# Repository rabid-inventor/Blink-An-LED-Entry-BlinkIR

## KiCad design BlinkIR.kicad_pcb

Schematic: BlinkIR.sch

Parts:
D1, D2, D3, D4: LED; LED_0805
J1, J2, J3: Conn_01x01; MountingHole_4.3mm_M4_ISO7380_Pad
Q1, Q2, Q3: Q_Photo_NPN; LED_D3.0mm_Horizontal_O1.27mm_Z2.0mm
R1, R3: 330R; R_0603
R2, R4: 10K; R_0603
TP1, TP2, TP3, TP4, TP5: TestPoint; Measurement_Point_Round-SMD-Pad_Small
U1: ATtiny10-TS; SOT-23-6

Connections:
/BLINK: R1.1, U1.4 (PB2)
/RESET: R2.1, TP2.1, U1.6 (~RESET~/PB3)
/SENCE_BLINK: Q1.1, Q2.1, Q3.1, R4.2, TP3.1, U1.1 (PB0)
/SEND_BLINK: D2.1, D3.1, D4.1, TP4.1, U1.3 (PB1)
GND: D1.1, J3.1, Q1.2, Q2.2, Q3.2, TP5.1, U1.2 (GND)
unnamed: D1.2, R1.2
unnamed: D2.2, D3.2, D4.2, R3.2
VCC: J1.1, J2.1, R2.2, R3.1, R4.1, TP1.1, U1.5 (VCC)

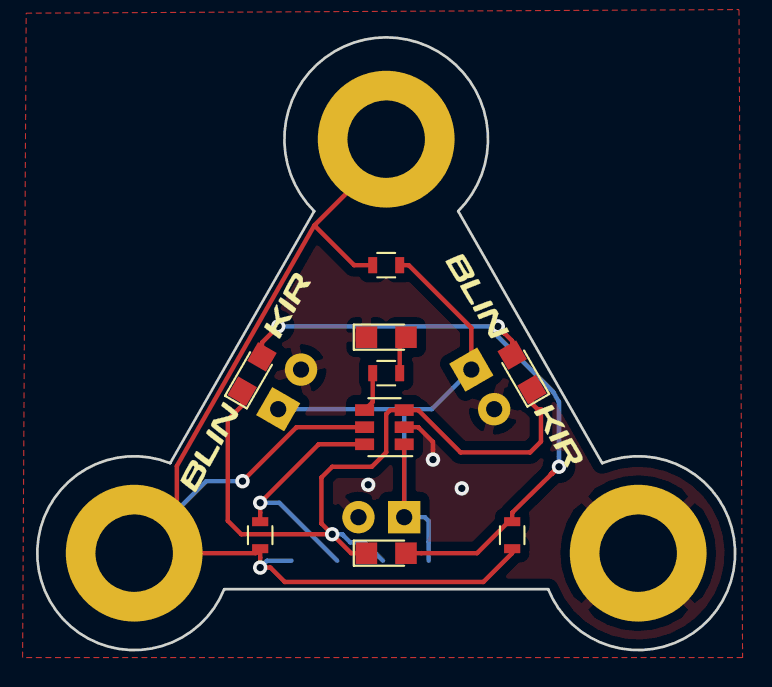
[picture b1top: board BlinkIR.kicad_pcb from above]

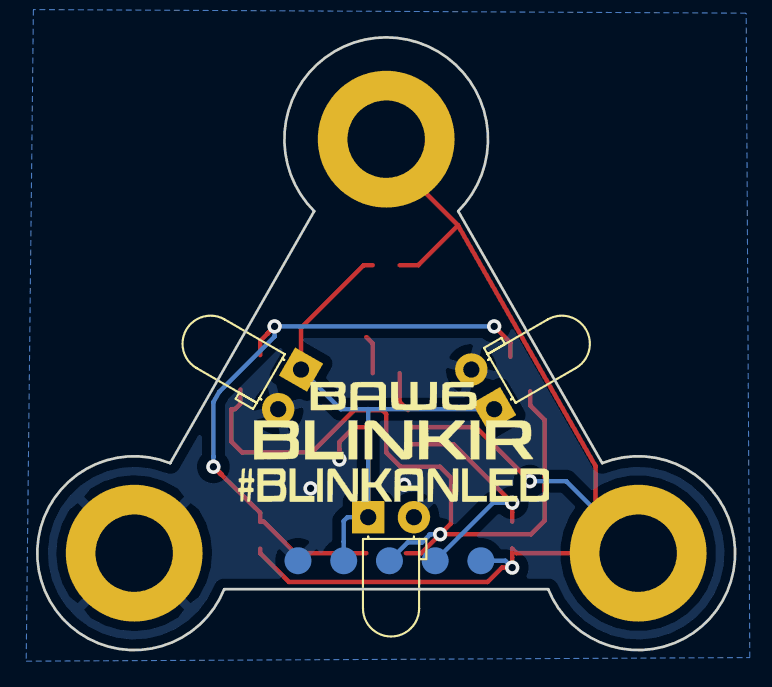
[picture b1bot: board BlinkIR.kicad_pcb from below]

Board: 2 copper layers, 38.8 x 34.0 mm, 20 parts (8 on the bottom side), 8 nets.

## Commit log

2018-08-29 Added initail files from board a week repo
2018-08-29 Project rename to BlinkIR
2018-08-31 started firmware
2018-09-02 added tiny soft serial library by ShaneG
    started experimenting with serial
2018-09-03 software retargeted to ATTiny10 and dropped uart Schmatic work finished rev1
2018-09-04 Finished PCB and generated Gerber
2018-09-08 Added final REV1 component vaules and tidied
2018-09-09 Finish working POC for revision 1 of BlinkIR
2018-09-14 small pinout tweeking in firmware
